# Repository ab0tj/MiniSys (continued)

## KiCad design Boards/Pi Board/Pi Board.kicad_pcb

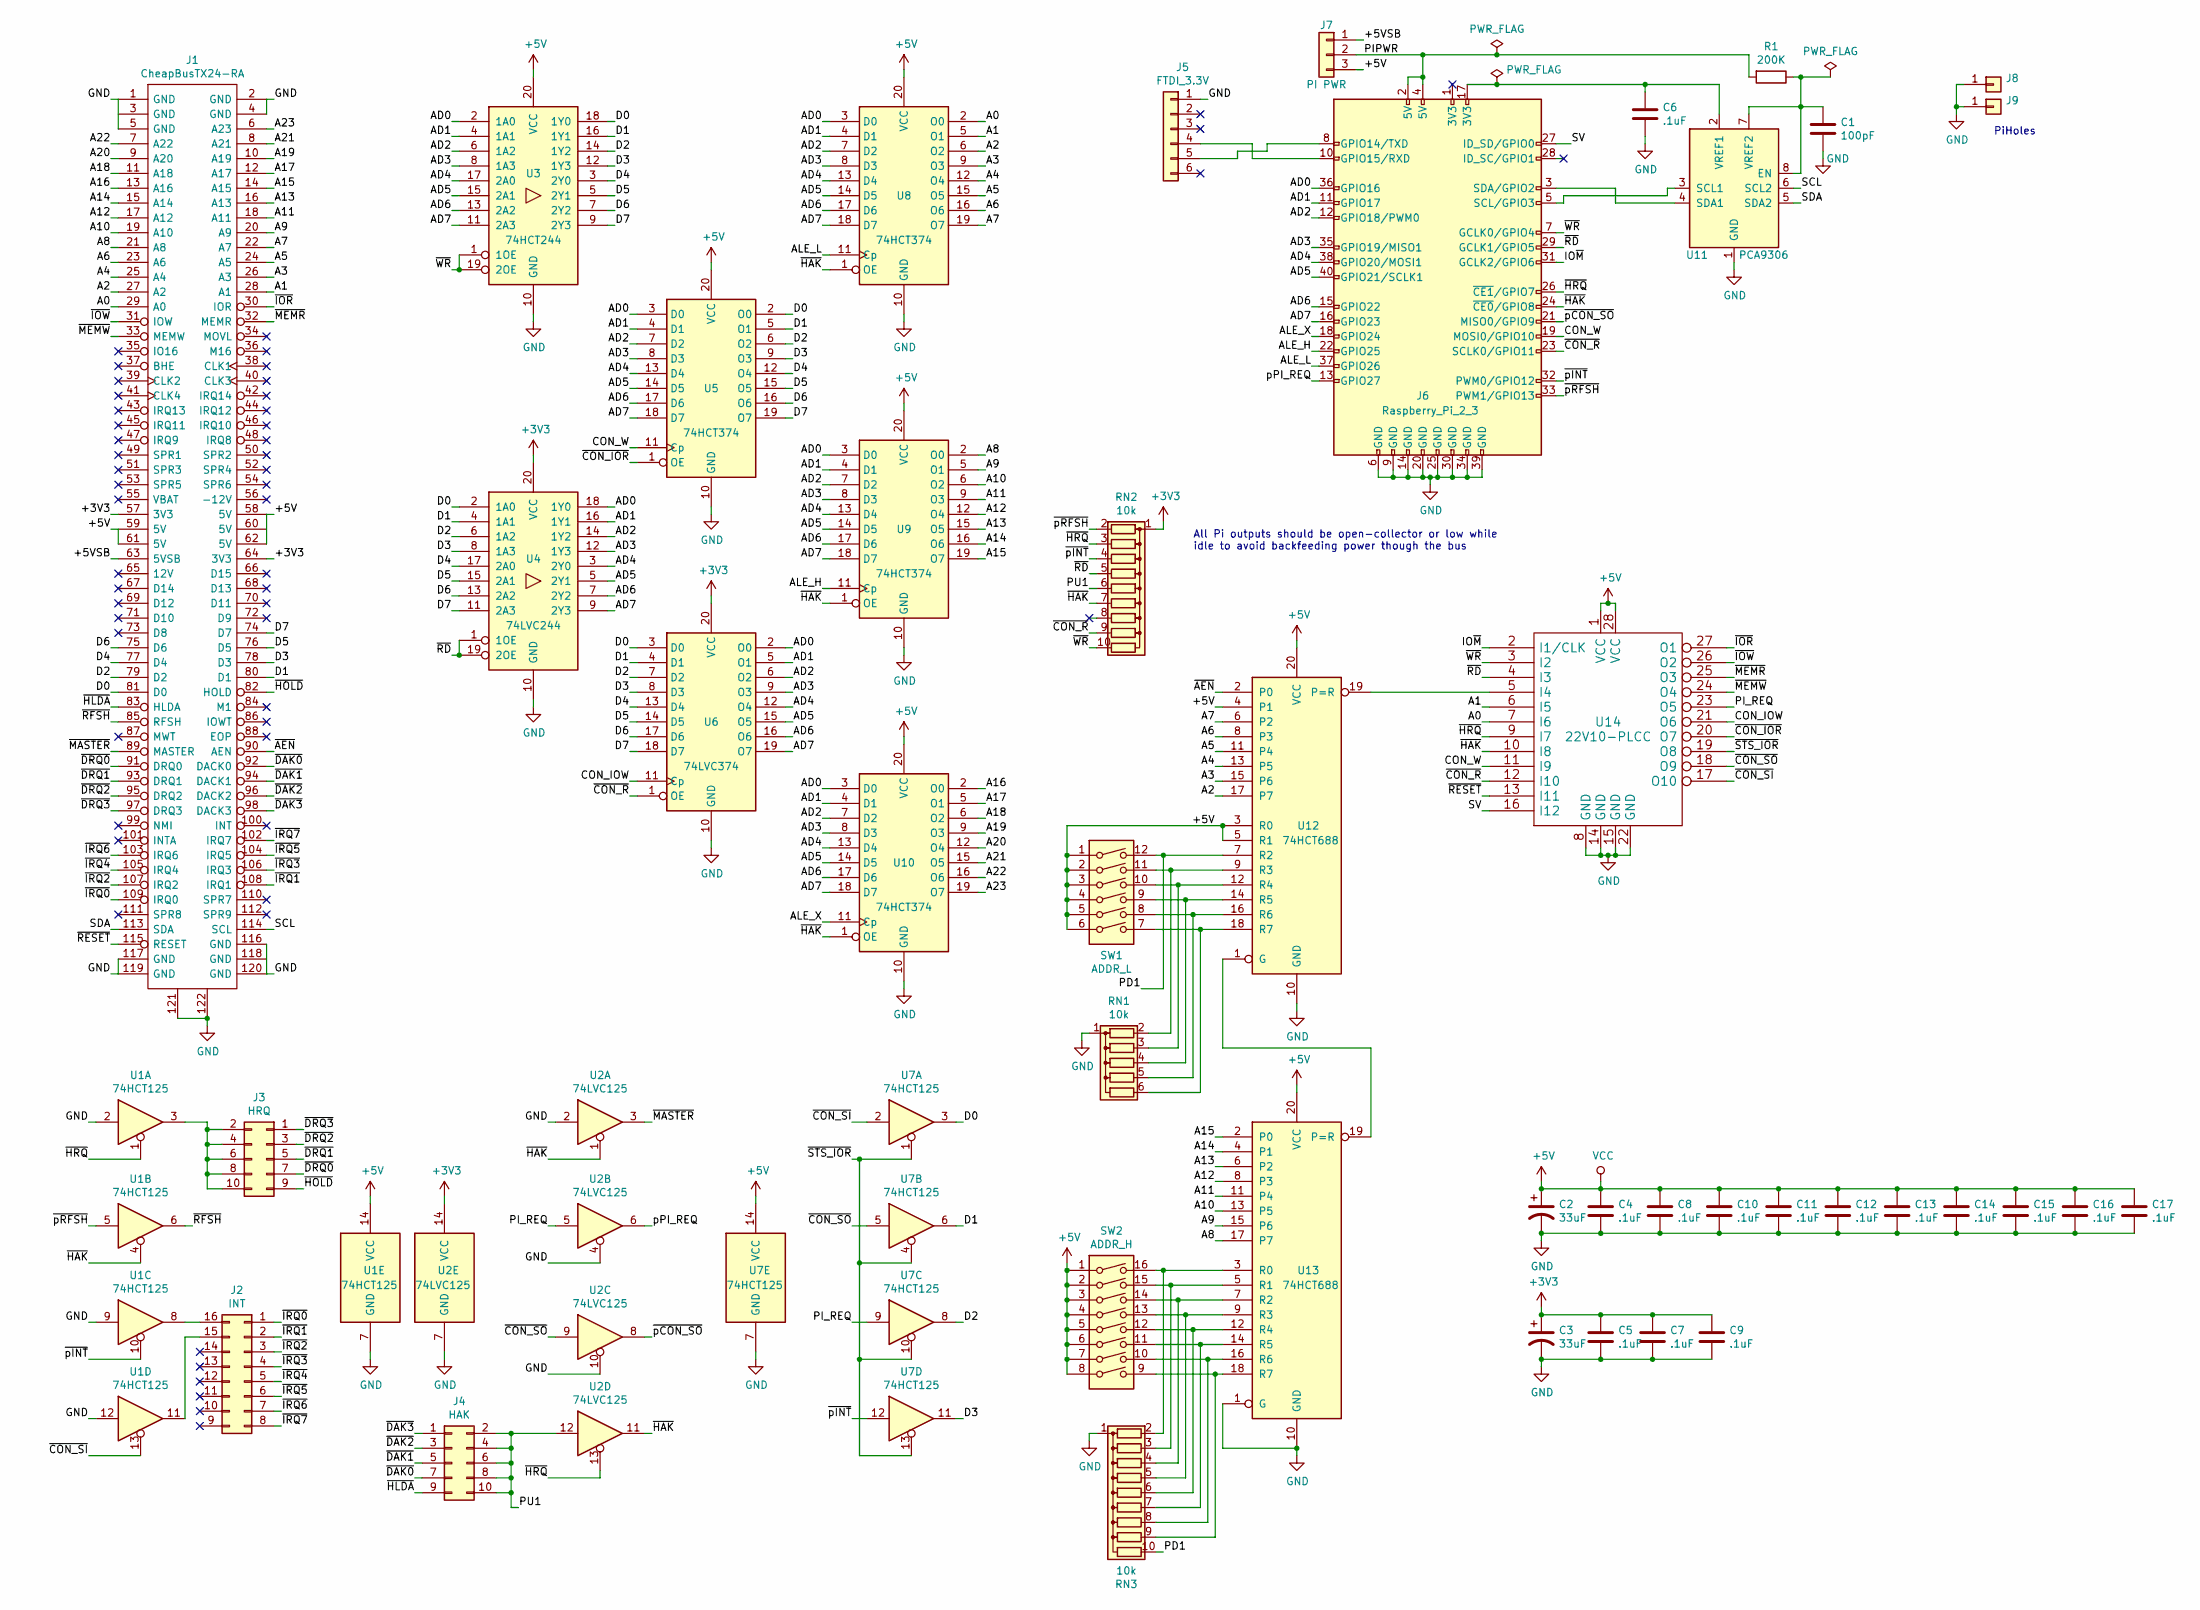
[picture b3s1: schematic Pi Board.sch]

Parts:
C1: 100pF; C_0805_HandSoldering
C2, C3: 33uF; CP_Tantalum_Case-B_EIA-3528-21_Hand
C4, C5, C6, C7, C8, C9, C10, C11, C12, C13, C14, C15, C16, C17: .1uF; C_0805_HandSoldering
J1: CheapBusTX24-RA; JAE_TX24-120R-LT-H1E; Mouser Part Number 656-TX24120RLTH1E
J2: INT; DIP-16_W7.62mm
J3: HRQ; Pin_Header_Straight_2x05_Pitch2.54mm
J4: HAK; Pin_Header_Straight_2x05_Pitch2.54mm
J5: FTDI_3.3V; Pin_Header_Angled_1x06_Pitch2.54mm
J6: Raspberry_Pi_2_3; Pin_Header_Straight_2x20_Pitch2.54mm
J7: PI PWR; Pin_Header_Straight_1x03_Pitch2.54mm
J8, J9: Conn_01x01; MountingHole_2.7mm_Pad_Via
R1: 200K; R_0805_HandSoldering
RN1: 10k; R_Array_SIP6
RN2, RN3: 10k; R_Array_SIP10
SW1: ADDR_L; SW_DIP_x6_W7.62mm_Slide
SW2: ADDR_H; SW_DIP_x8_W7.62mm_Slide
U1, U7: 74HCT125; SOIC-14_3.9x8.7mm_Pitch1.27mm
U2: 74LVC125; SOIC-14_3.9x8.7mm_Pitch1.27mm
U3: 74HCT244; SOIC-20W_7.5x12.8mm_Pitch1.27mm
U4: 74LVC244; SOIC-20W_7.5x12.8mm_Pitch1.27mm
U5, U8, U9, U10: 74HCT374; SOIC-20W_7.5x12.8mm_Pitch1.27mm
U6: 74LVC374; SOIC-20W_7.5x12.8mm_Pitch1.27mm
U11: PCA9306; SOIC-8_3.9x4.9mm_Pitch1.27mm
U12, U13: 74HCT688; SOIC-20W_7.5x12.8mm_Pitch1.27mm
U14: 22V10-PLCC; PLCC28

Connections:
+3V3: C3.1, C5.1, C7.1, C9.1, J1.57 (3V3), J1.64 (3V3), RN2.1 (common), U2.14 (VCC), U4.20 (VCC), U6.20 (VCC)
+5V: C2.1, C4.1, C8.1, C10.1, C11.1, C12.1, C13.1, C14.1, C15.1, C16.1, C17.1, J1.58 (5V), J1.59 (5V), J1.60 (5V), J1.61 (5V), J1.62 (5V), J7.3, SW1.1, SW1.2, SW1.3, SW1.4, SW1.5, SW1.6, SW2.1, SW2.2, SW2.3, SW2.4, SW2.5, SW2.6, SW2.7, SW2.8, U1.14 (VCC), U3.20 (VCC), U5.20 (VCC), U7.14 (VCC), U8.20 (VCC), U9.20 (VCC), U10.20 (VCC), U12.3 (R0), U12.4 (P1), U12.5 (R1), U12.20 (VCC), U13.20 (VCC), U14.1 (VCC), U14.28 (VCC)
/+5VSB: J1.63 (5VSB), J7.1
/A0: J1.29 (A0), U8.2 (O0), U14.7 (I6)
/A1: J1.28 (A1), U8.5 (O1), U14.6 (I5)
/A2: J1.27 (A2), U8.6 (O2), U12.17 (P7)
/A3: J1.26 (A3), U8.9 (O3), U12.15 (P6)
/A4: J1.25 (A4), U8.12 (O4), U12.13 (P5)
/A5: J1.24 (A5), U8.15 (O5), U12.11 (P4)
/A6: J1.23 (A6), U8.16 (O6), U12.8 (P3)
/A7: J1.22 (A7), U8.19 (O7), U12.6 (P2)
/A8: J1.21 (A8), U9.2 (O0), U13.17 (P7)
/A9: J1.20 (A9), U9.5 (O1), U13.15 (P6)
/A10: J1.19 (A10), U9.6 (O2), U13.13 (P5)
/A11: J1.18 (A11), U9.9 (O3), U13.11 (P4)
/A12: J1.17 (A12), U9.12 (O4), U13.8 (P3)
/A13: J1.16 (A13), U9.15 (O5), U13.6 (P2)
/A14: J1.15 (A14), U9.16 (O6), U13.4 (P1)
/A15: J1.14 (A15), U9.19 (O7), U13.2 (P0)
/A16: J1.13 (A16), U10.2 (O0)
/A17: J1.12 (A17), U10.5 (O1)
/A18: J1.11 (A18), U10.6 (O2)
/A19: J1.10 (A19), U10.9 (O3)
/A20: J1.9 (A20), U10.12 (O4)
/A21: J1.8 (A21), U10.15 (O5)
/A22: J1.7 (A22), U10.16 (O6)
/A23: J1.6 (A23), U10.19 (O7)
/AD0: J6.36 (GPIO16), U3.2 (1A0), U4.18 (1Y0), U5.3 (D0), U6.2 (O0), U8.3 (D0), U9.3 (D0), U10.3 (D0)
/AD1: J6.11 (GPIO17), U3.4 (1A1), U4.16 (1Y1), U5.4 (D1), U6.5 (O1), U8.4 (D1), U9.4 (D1), U10.4 (D1)
/AD2: J6.12 (GPIO18/PWM0), U3.6 (1A2), U4.14 (1Y2), U5.7 (D2), U6.6 (O2), U8.7 (D2), U9.7 (D2), U10.7 (D2)
/AD3: J6.35 (GPIO19/MISO1), U3.8 (1A3), U4.12 (1Y3), U5.8 (D3), U6.9 (O3), U8.8 (D3), U9.8 (D3), U10.8 (D3)
/AD4: J6.38 (GPIO20/MOSI1), U3.17 (2A0), U4.3 (2Y0), U5.13 (D4), U6.12 (O4), U8.13 (D4), U9.13 (D4), U10.13 (D4)
/AD5: J6.40 (GPIO21/SCLK1), U3.15 (2A1), U4.5 (2Y1), U5.14 (D5), U6.15 (O5), U8.14 (D5), U9.14 (D5), U10.14 (D5)
/AD6: J6.15 (GPIO22), U3.13 (2A2), U4.7 (2Y2), U5.17 (D6), U6.16 (O6), U8.17 (D6), U9.17 (D6), U10.17 (D6)
/AD7: J6.16 (GPIO23), U3.11 (2A3), U4.9 (2Y3), U5.18 (D7), U6.19 (O7), U8.18 (D7), U9.18 (D7), U10.18 (D7)
/ALE_H: J6.22 (GPIO25), U9.11 (Cp)
/ALE_L: J6.37 (GPIO26), U8.11 (Cp)
/ALE_X: J6.18 (GPIO24), U10.11 (Cp)
/CON_IOW: U6.11 (Cp), U14.21 (O6)
/CON_W: J6.19 (MOSI0/GPIO10), U5.11 (Cp), U14.11 (I9)
/D0: J1.81 (D0), U3.18 (1Y0), U4.2 (1A0), U5.2 (O0), U6.3 (D0), U7.3
/D1: J1.80 (D1), U3.16 (1Y1), U4.4 (1A1), U5.5 (O1), U6.4 (D1), U7.6
/D2: J1.79 (D2), U3.14 (1Y2), U4.6 (1A2), U5.6 (O2), U6.7 (D2), U7.8
/D3: J1.78 (D3), U3.12 (1Y3), U4.8 (1A3), U5.9 (O3), U6.8 (D3), U7.11
/D4: J1.77 (D4), U3.3 (2Y0), U4.17 (2A0), U5.12 (O4), U6.13 (D4)
/D5: J1.76 (D5), U3.5 (2Y1), U4.15 (2A1), U5.15 (O5), U6.14 (D5)
/D6: J1.75 (D6), U3.7 (2Y2), U4.13 (2A2), U5.16 (O6), U6.17 (D6)
/D7: J1.74 (D7), U3.9 (2Y3), U4.11 (2A3), U5.19 (O7), U6.18 (D7)
/IO~M: J6.31 (GCLK2/GPIO6), U14.2 (I1/CLK)
/PD1: RN3.10 (R9), SW1.12, U12.7 (R2)
/PIPWR: J6.2 (5V), J6.4 (5V), J7.2, R1.2
/PI_REQ: U2.5, U7.9, U14.23 (O5)
/PU1: J4.2, J4.4, J4.6, J4.8, J4.10, RN2.6 (R5), U2.12
/SCL: J1.114 (SCL), U11.6 (SCL2)
/SDA: J1.113 (SDA), U11.5 (SDA2)
/pPI_REQ: J6.13 (GPIO27), U2.6
/~AEN: J1.90 (AEN), U12.2 (P0)
/~CON_IOR: U5.1 (OE), U14.20 (O7)
/~CON_R: J6.23 (SCLK0/GPIO11), RN2.9 (R8), U6.1 (OE), U14.12 (I10)
/~CON_SI: U1.13, U7.2, U14.17 (O10)
/~CON_SO: U2.9, U7.5, U14.18 (O9)
/~DAK0: J1.92 (DACK0), J4.7
/~DAK1: J1.94 (DACK1), J4.5
/~DAK2: J1.96 (DACK2), J4.3
/~DAK3: J1.98 (DACK3), J4.1
/~DRQ0: J1.91 (DRQ0), J3.7
/~DRQ1: J1.93 (DRQ1), J3.5
/~DRQ2: J1.95 (DRQ2), J3.3
/~DRQ3: J1.97 (DRQ3), J3.1
/~HAK: J6.24 (~CE0~/GPIO8), RN2.7 (R6), U1.4, U2.1, U2.11, U8.1 (OE), U9.1 (OE), U10.1 (OE), U14.10 (I8)
/~HLDA: J1.83 (HLDA), J4.9
/~HOLD: J1.82 (HOLD), J3.9
/~HRQ: J6.26 (~CE1~/GPIO7), RN2.3 (R2), U1.1, U2.13, U14.9 (I7)
/~IOR: J1.30 (IOR), U14.27 (O1)
/~IOW: J1.31 (IOW), U14.26 (O2)
/~IRQ0: J1.109 (IRQ0), J2.1
/~IRQ1: J1.108 (IRQ1), J2.2
/~IRQ2: J1.107 (IRQ2), J2.3
/~IRQ3: J1.106 (IRQ3), J2.4
/~IRQ4: J1.105 (IRQ4), J2.5
/~IRQ5: J1.104 (IRQ5), J2.6
/~IRQ6: J1.103 (IRQ6), J2.7
/~IRQ7: J1.102 (IRQ7), J2.8
/~MASTER: J1.89 (MASTER), U2.3
/~MEMR: J1.32 (MEMR), U14.25 (O3)
/~MEMW: J1.33 (MEMW), U14.24 (O4)
/~RD: J6.29 (GCLK1/GPIO5), RN2.5 (R4), U4.1 (1OE), U4.19 (2OE), U14.4 (I3)
/~RESET: J1.115 (RESET), U14.13 (I11)
/~RFSH: J1.85 (RFSH), U1.6
/~STS_IOR: U7.1, U7.4, U7.10, U7.13, U14.19 (O8)
/~WR: J6.7 (GCLK0/GPIO4), RN2.10 (R9), U3.1 (1OE), U3.19 (2OE), U14.3 (I2)
/~pCON_SO: J6.21 (MISO0/GPIO9), U2.8
/~pINT: J6.32 (PWM0/GPIO12), RN2.4 (R3), U1.10, U7.12
/~pRFSH: J6.33 (PWM1/GPIO13), RN2.2 (R1), U1.5
unnamed: C1.1, R1.1, U11.7 (VREF2), U11.8 (EN)
unnamed: C6.1, J6.17 (3V3), U11.2 (VREF1)
unnamed: J2.15, U1.11
unnamed: J2.16, U1.8
unnamed: J3.2, J3.4, J3.6, J3.8, J3.10, U1.3
unnamed: J5.4, J6.10 (GPIO15/RXD)
unnamed: J5.5, J6.8 (GPIO14/TXD)
unnamed: J6.3 (SDA/GPIO2), U11.4 (SDA1)
unnamed: J6.5 (SCL/GPIO3), U11.3 (SCL1)
unnamed: RN1.2 (R1), SW1.11, U12.9 (R3)
unnamed: RN1.3 (R2), SW1.10, U12.12 (R4)
unnamed: RN1.4 (R3), SW1.9, U12.14 (R5)
unnamed: RN1.5 (R4), SW1.8, U12.16 (R6)
unnamed: RN1.6 (R5), SW1.7, U12.18 (R7)
unnamed: RN3.2 (R1), SW2.16, U13.3 (R0)
unnamed: RN3.3 (R2), SW2.15, U13.5 (R1)
unnamed: RN3.4 (R3), SW2.14, U13.7 (R2)
unnamed: RN3.5 (R4), SW2.13, U13.9 (R3)
unnamed: RN3.6 (R5), SW2.12, U13.12 (R4)
unnamed: RN3.7 (R6), SW2.11, U13.14 (R5)
unnamed: RN3.8 (R7), SW2.10, U13.16 (R6)
unnamed: RN3.9 (R8), SW2.9, U13.18 (R7)
unnamed: U12.1 (G), U13.19 (P=R)
unnamed: U12.19 (P=R), U14.5 (I4)

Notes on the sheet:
PiHoles
All Pi outputs should be open-collector or low while idle to avoid backfeeding power though the bus

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
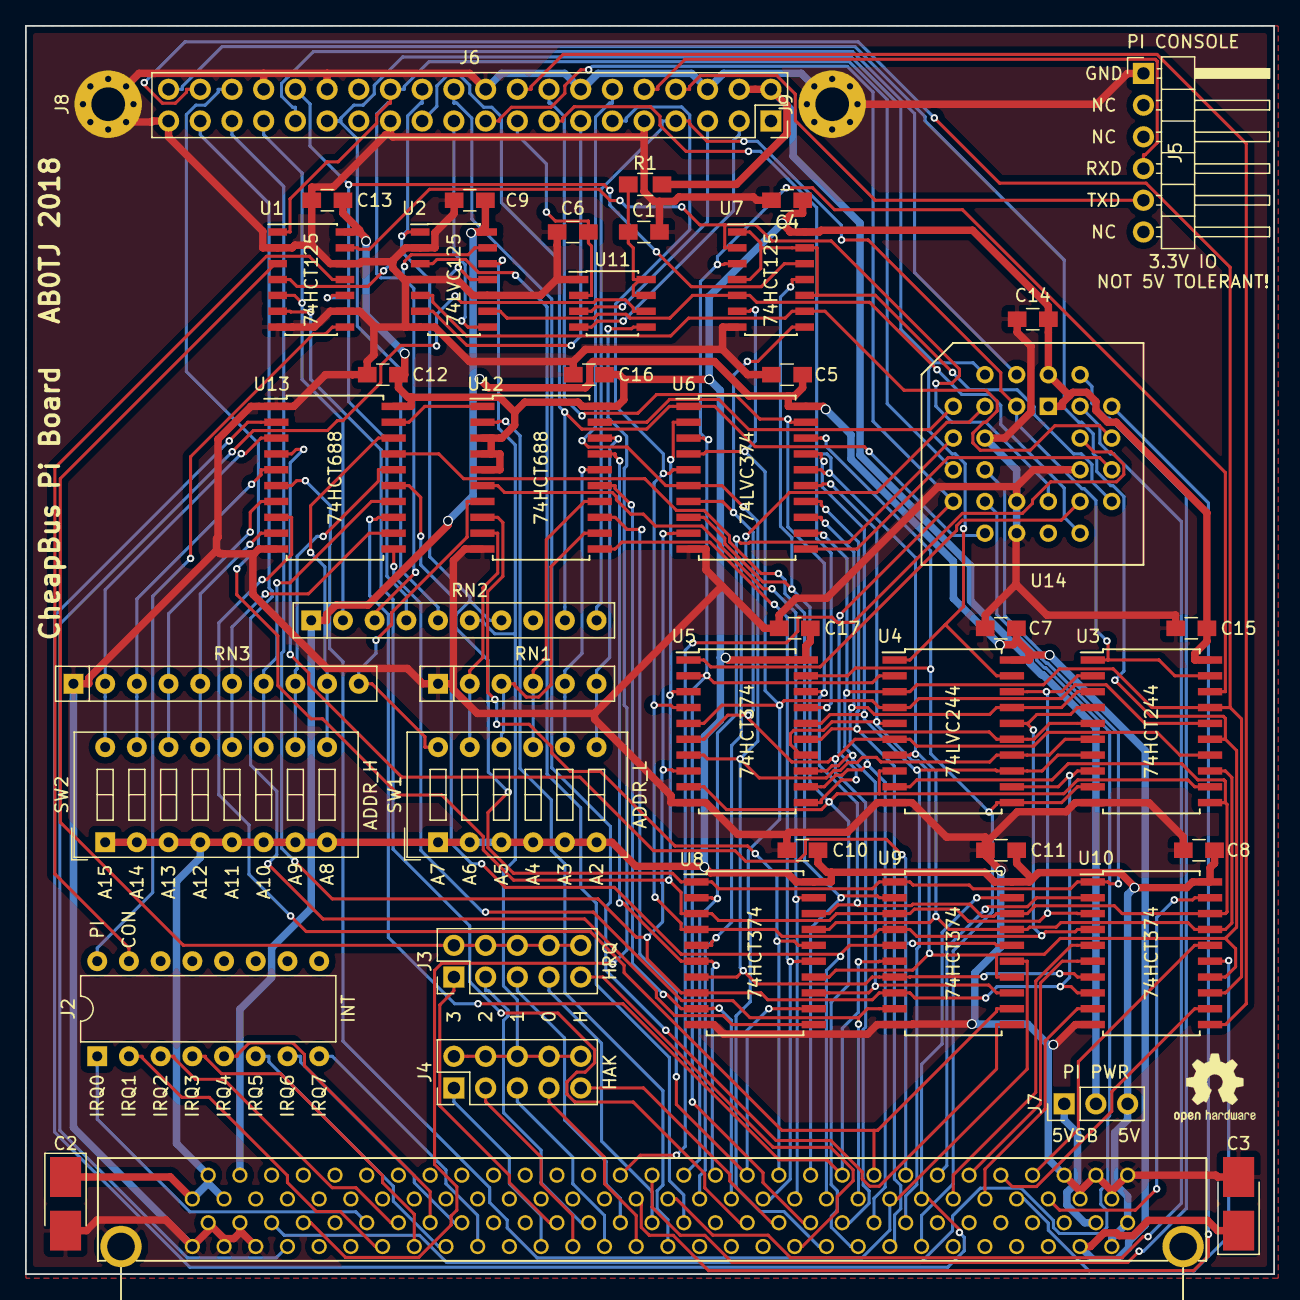
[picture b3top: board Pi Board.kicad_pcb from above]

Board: 2 copper layers, 100.0 x 100.0 mm, 46 parts (0 on the bottom side), 119 nets.
